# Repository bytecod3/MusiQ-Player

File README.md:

## MusiQ-Player
An MP3 player clone built on ESP32

### Motivation 
To replicate a simpler and/or close-to version of the common MP3 player already in the market using readily available hardware. 
To implement a Finite State Machine on an electronic consumer product

### State Diagram

### Block Diagram

### Stack
1. C++
2. PlatformIO

### Schematic

### PCB Design 

### 3D casing design

The STEP files for 3D printing can be found in the ```3D``` Folder, named ```casing-step.stp```.

### Parts List 
1. ESP32 WROOM
2. 0.96" OLED screen
3. 5 tactile switches
4. 2 3.7V LP945170 LIPO batteries 
5. Micro SD card reader module (alternative:MicroSD card socket)
6. 74HC14 Schmitt trigger IC
7. USB Cable (Type C or B)
8. Protoboards
9. TP4056 charging module
10. MAX98357 Amplifier module

### References 
1. https://www.studiopieters.nl/esp32-program-a-esp32/
2. https://circuitdigest.com/microcontroller-projects/esp32-based-internet-radio-using-max98357a-i2s-amplifier-board
3. https://learn.adafruit.com/assets/32642
4. https://docs.espressif.com/projects/esp-idf/en/v4.4/esp32c3/api-reference/peripherals/i2s.html

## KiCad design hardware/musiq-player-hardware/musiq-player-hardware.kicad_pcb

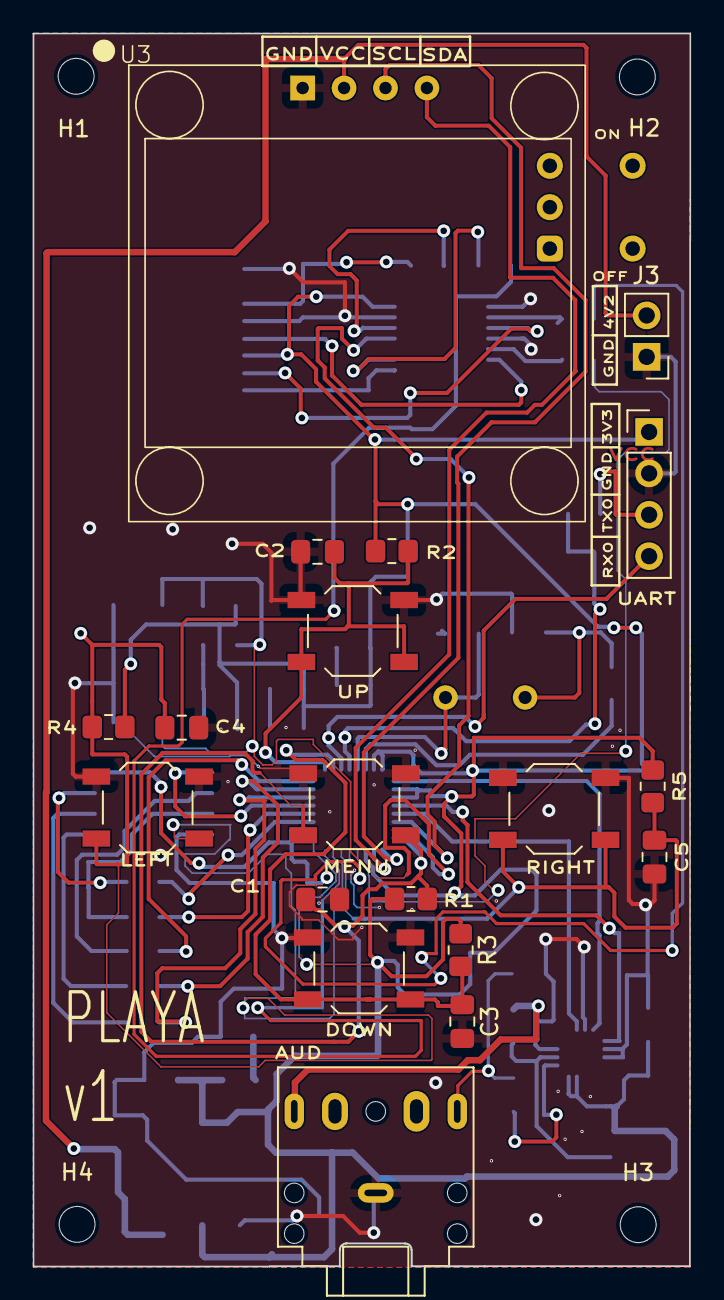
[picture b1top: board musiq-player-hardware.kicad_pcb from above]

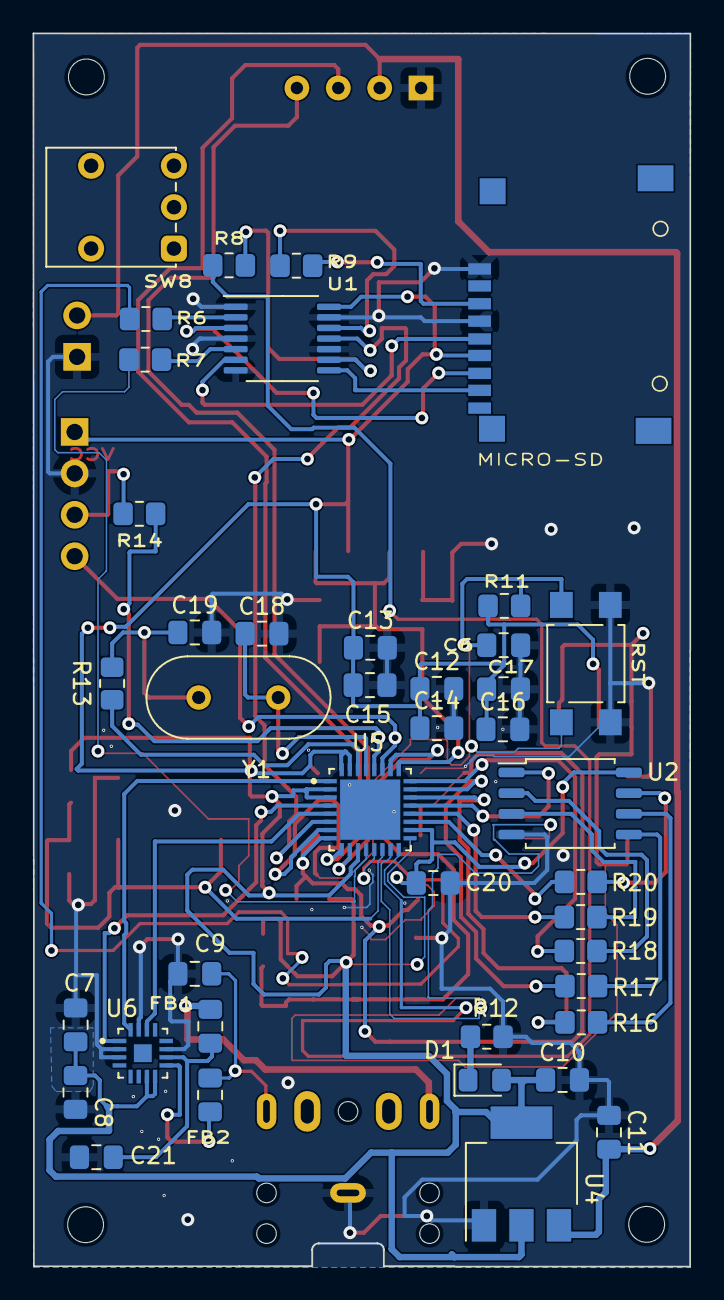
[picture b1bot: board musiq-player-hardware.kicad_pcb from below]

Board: 2 copper layers, 40.3 x 75.6 mm, 64 parts (41 on the bottom side), 49 nets.

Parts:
AUD: AudioJack3; Jack_3.5mm_CUI_SJ1-3525N_Horizontal
C1, C2, C3, C4, C5, C10, C11, C12, C13, C14, C16, C17: 100nF; C_0805_2012Metric_Pad1.18x1.45mm_HandSolder
C6: 100nF/50V; C_0805_2012Metric_Pad1.18x1.45mm_HandSolder
C7: 10uF; C_0805_2012Metric_Pad1.18x1.45mm_HandSolder
C8: 0.1uF; C_0805_2012Metric_Pad1.18x1.45mm_HandSolder
C9, C21: 220pF; C_0805_2012Metric_Pad1.18x1.45mm_HandSolder
C15, C20: 1uF; C_0805_2012Metric_Pad1.18x1.45mm_HandSolder
C18, C19: 22pF; C_0805_2012Metric_Pad1.18x1.45mm_HandSolder
D1: LED; LED_0805_2012Metric_Pad1.15x1.40mm_HandSolder
DOWN: SW_MEC_5E; SW_SPST_TL3342
FB1, FB2: FerriteBead; C_0805_2012Metric_Pad1.18x1.45mm_HandSolder
H1, H2, H3, H4: MountingHole; MountingHole_2.2mm_M2
J3: TP4056_CONN; PinHeader_1x02_P2.54mm_Vertical
LEFT: SW_MEC_5E; SW_SPST_TL3342
MENU: SW_MEC_5E; SW_SPST_TL3342
MICRO-SD: Micro_SD_Card; SD-CARD-Adapter-alibaba
R1, R2, R3, R4, R5, R13, R16, R17, R18, R19, R20: 10k; R_0805_2012Metric_Pad1.20x1.40mm_HandSolder
R6, R7, R8, R9: 3.3k; R_0805_2012Metric_Pad1.20x1.40mm_HandSolder
R11: 10k/5%; R_0805_2012Metric_Pad1.20x1.40mm_HandSolder
R12: 220R; R_0805_2012Metric_Pad1.20x1.40mm_HandSolder
R14: 499R; R_0805_2012Metric_Pad1.20x1.40mm_HandSolder
RIGHT: SW_MEC_5E; SW_SPST_TL3342
RST: RST; SW_SPST_TL3305A
SW8: ON/OFF; SW_Push_1P2T_Vertical_E-Switch_800UDP8P1A1M6
U1: 74LVC125; TSSOP-14_4.4x5mm_P0.65mm
U2: W25Q128JVS; SOIC-8_5.23x5.23mm_P1.27mm
U3: oled-ssd1306
U4: AMS1117-3.3; SOT-223-3_TabPin2
U5: ESP32C3; QFN32_5X5MM
U6: MAX98357AETE; QFN50P300X300X80-17N
UART: UART; PinHeader_1x04_P2.54mm_Vertical
UP: SW_MEC_5E; SW_SPST_TL3342
Y1: 40MHz; Crystal_HC49-U_Vertical

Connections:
+3V3: C7.1, C8.1, C10.1, C12.1, C13.1, C14.1, C15.1, C16.1, C17.1, D1.2 (A), MICRO-SD.4 (VDD), R1.1, R2.1, R3.1, R4.1, R5.1, R11.1, U1.14 (VCC), U4.2 (VO), U5.2 (VDD3P3), U5.3 (VDD3P3), U5.11 (VDD3P3_RTC), U5.17 (VDD3P3_CPU), U5.31 (VDDA), U5.32 (VDDA), U6.7 (VDD), U6.8 (VDD), UART.1
/4.2V_BATT: C11.1, J3.2, U3.2 (VCC), U4.3 (VI)
/AUD_N: AUD.R, FB1.2
/AUD_P: AUD.T, C9.1, FB2.2
/BCLK: U5.1 (LNA_IN), U6.16 (BCLK)
/DIN: U5.4 (XTAL_32K_P), U6.1 (DIN)
/DOWN_BTN: C3.1, DOWN.2 (A), R3.2, U5.26 (GPIO19)
/LEFT_BTN: C4.1, LEFT.2 (A), R4.2, U5.15 (GPIO9)
/LRCLK: U5.5 (XTAL_32K_N), U6.14 (LRCLK)
/MENU_BTN: C1.1, MENU.2 (A), R1.2, U5.8 (GPIO3)
/RIGHT_BTN: C5.1, R5.2, RIGHT.2 (A), U5.14 (GPIO8)
/SCL: U3.3 (SCL), U5.9 (MTMS)
/SDA: U3.4 (SDA), U5.10 (MTDI)
/SD_CS: R8.1, U5.16 (GPIO10)
/SD_MISO: U1.11, U5.6 (GPIO2)
/SD_MOSI: R6.1, U5.13 (MTDO)
/SD_SCK: R7.1, U5.12 (MTCK)
/UP_BTN: C2.1, R2.2, U5.25 (GPIO18), UP.2 (A)
/VDD_SPI: C20.1, U2.8 (VCC), U5.18 (VDD_SPI)
GND: AUD.S, C1.2, C2.2, C3.2, C4.2, C5.2, C6.2, C7.2, C8.2, C9.2, C10.2, C11.2, C12.2, C13.2, C14.2, C15.2, C16.2, C17.2, C18.2, C19.2, C20.2, C21.2, DOWN.1, J3.1, LEFT.1, MENU.1, MICRO-SD.6 (VSS), MICRO-SD.9 (SHIELD), R12.2, RIGHT.1, RST.1, U1.1, U1.4, U1.7 (GND), U1.10, U1.13, U2.4 (GND), U3.1 (GND), U4.1 (GND), U5.33 (GND), U6.2 (GAIN_SLOT), U6.3 (GND), U6.11 (GND), U6.15 (GND), UART.2, UP.1
unnamed: C19.1, R13.1, Y1.2
unnamed: D1.1 (K), R12.1
unnamed: MICRO-SD.5 (CLK), U1.6
unnamed: MICRO-SD.3 (CMD), U1.3
unnamed: MICRO-SD.7 (DAT0), R9.1
unnamed: MICRO-SD.2 (DAT3/CD), U1.8
unnamed: R14.2, UART.3
unnamed: U5.27 (U0RXD), UART.4
unnamed: R6.2, U1.2
unnamed: R7.2, U1.5
unnamed: R8.2, U1.9
unnamed: R9.2, U1.12
unnamed: C6.1, R11.2, RST.2 (A), U5.7 (CHIP_EN)
unnamed: R16.1, U2.6 (CLK)
unnamed: R17.1, U2.5 (DI(IO0))
unnamed: R18.1, U2.2 (DO(IO1))
unnamed: R19.1, U2.3 (IO2)
unnamed: R20.1, U2.7 (IO3)
unnamed: U2.1 (~CS), U5.21 (SPICS0)
unnamed: R16.2, U5.22 (SPICLK)
unnamed: R17.2, U5.23 (SPID)
unnamed: R20.2, U5.19 (SPIHD)
unnamed: R18.2, U5.24 (SPIQ)
unnamed: R19.2, U5.20 (SPIWP)
unnamed: R14.1, U5.28 (U0TXD)
unnamed: C18.1, U5.29 (XTAL_N), Y1.1
unnamed: R13.2, U5.30 (XTAL_P)
unnamed: C21.1, FB1.1, U6.10 (OUTN)
unnamed: FB2.1, U6.9 (OUTP)

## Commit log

2024-02-27 adds function prototypes
2024-02-29 adds platformio proejct structure
2024-02-29 adds esp32 toolkit
2024-02-29 adds menu page 1
2024-03-01 adds working menu
2024-03-01 adds button class
2024-03-02 adds right debounce time
2024-03-02 adds interrupt initialization
2024-03-02 adds finite state machine
2024-03-03 fixes menu home selection
2024-03-03 adds SD card functions
2024-03-03 adds SD card info
2024-03-03 FIXES: icons array indexing
2024-03-03 adds dynamic music list creation
2024-03-04 adds list music memory allocation
2024-03-04 adds working music list
2024-03-04 adds state diagram
2024-03-05 adds PLAYING state
2024-03-07 adds playing screen animation
2024-03-07 adds settings menu
2024-03-07 adds working settings menu
2024-03-07 FIXES: music list indexing issue
2024-03-07 adds final playing screen animation
2024-03-11 adds shuffle menu with namespace storage
2024-03-11 adds updateSettings Function
2024-03-12 adds sd card module and esp-pico-d4
2024-03-12 adds on/off switch schematic
2024-03-13 adds splash screen
2024-03-13 adds block diagram
2024-03-15 adds esp32-c3 schematic
2024-03-20 complete schematic diagram
2024-03-26 adds complete PCB
2024-03-26 adds final PCB renders
2024-03-26 adds 3D design files
